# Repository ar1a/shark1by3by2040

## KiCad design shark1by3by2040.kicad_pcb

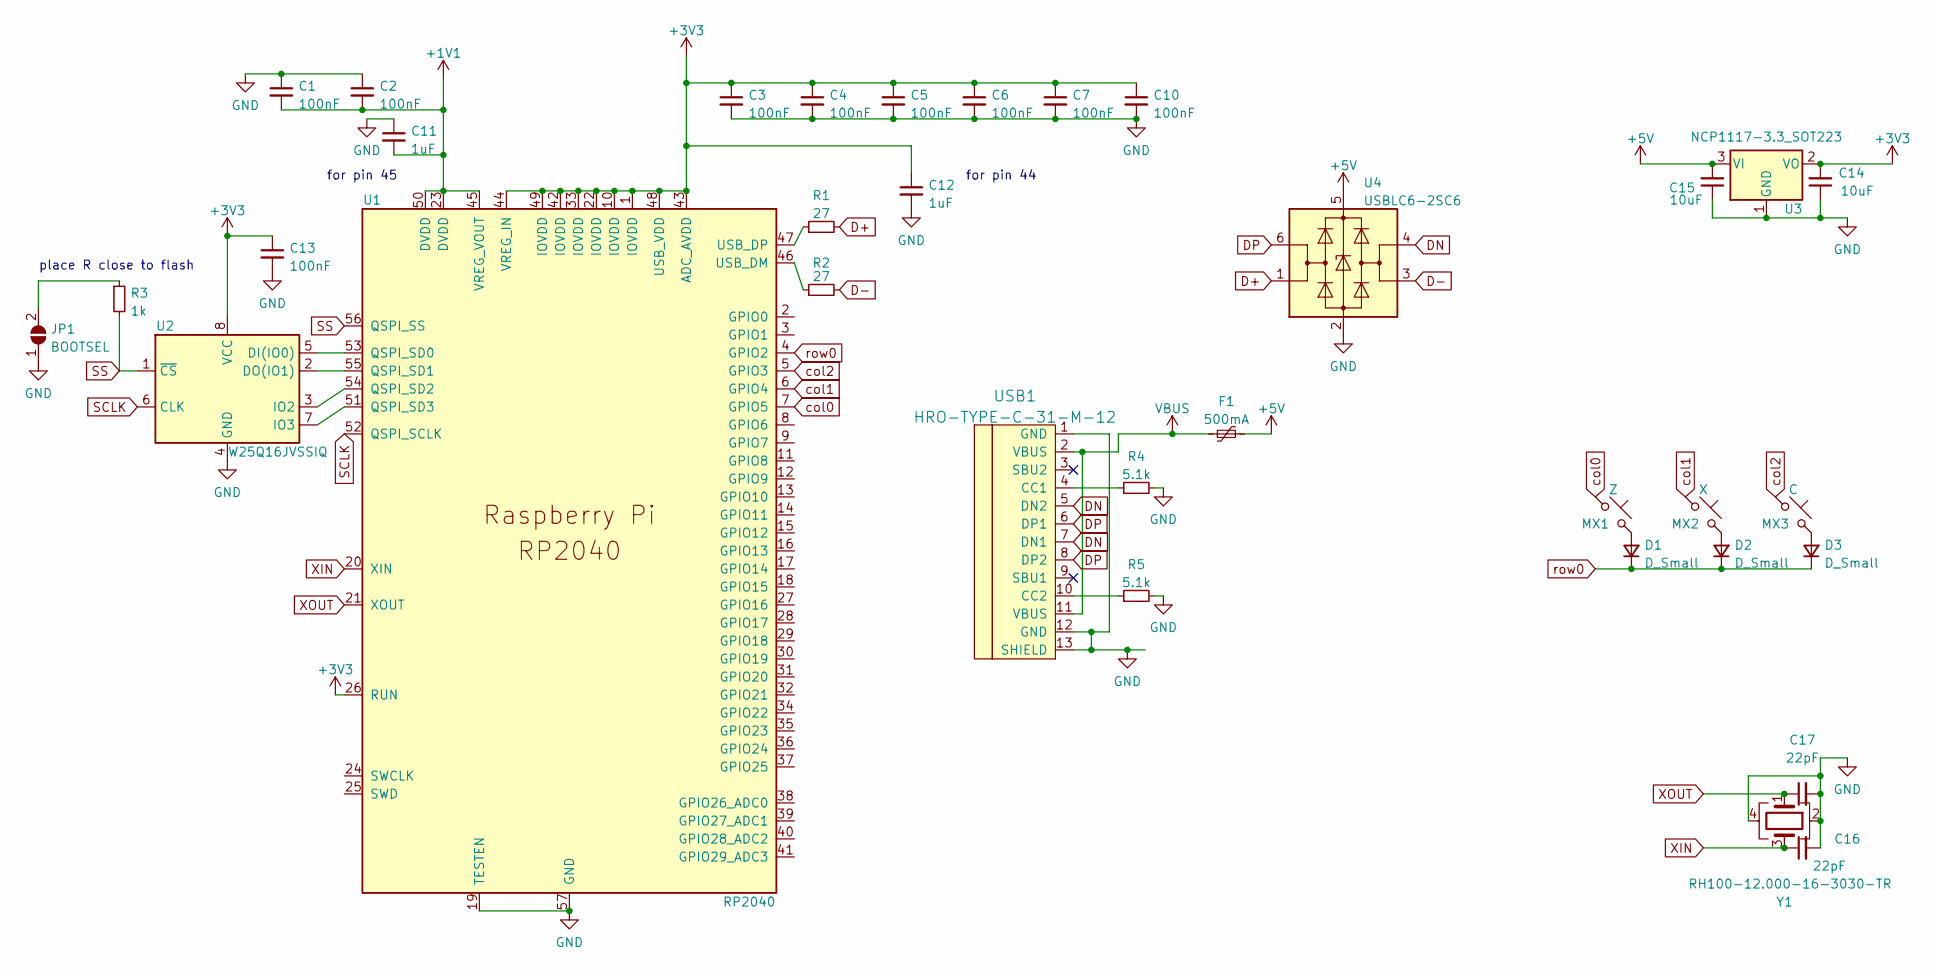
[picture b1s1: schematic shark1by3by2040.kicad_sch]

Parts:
C1, C2, C3, C4, C5, C6, C7, C10, C13: 100nF; C_0402_1005Metric
C11, C12: 1uF; C_0402_1005Metric
C14, C15: 10uF; C_0402_1005Metric
C16, C17: 22pF; C_0402_1005Metric
D1, D2, D3: D_Small; D_SOD-123-Pretty
F1: 500mA; Fuse_0805_2012Metric
JP1: BOOTSEL; Jumper-UserFriendly-Small
MX1: Z; SW_MX_HS_1u
MX2: X; SW_MX_HS_1u
MX3: C; SW_MX_HS_1u
R1, R2: 27; R_0402_1005Metric
R3: 1k; R_0402_1005Metric
R4, R5: 5.1k; R_0402_1005Metric
U1: RP2040; RP2040-QFN-56
U2: W25Q16JVSSIQ; SOIC-8_5.23x5.23mm_P1.27mm
U3: NCP1117-3.3_SOT223; SOT-223-3_TabPin2
U4: USBLC6-2SC6; SOT-23-6
USB1: HRO-TYPE-C-31-M-12; HRO-TYPE-C-31-M-12-Assembly
Y1: RH100-12.000-16-3030-TR; Crystal_SMD_3225-4Pin_3.2x2.5mm

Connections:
+1V1: C1.2, C2.2, C11.2, U1.23 (DVDD), U1.45 (VREG_VOUT), U1.50 (DVDD)
+3V3: C3.1, C4.1, C5.1, C6.1, C7.1, C10.1, C12.1, C13.1, C14.2, U1.1 (IOVDD), U1.10 (IOVDD), U1.22 (IOVDD), U1.26 (RUN), U1.33 (IOVDD), U1.42 (IOVDD), U1.43 (ADC_AVDD), U1.44 (VREG_IN), U1.48 (USB_VDD), U1.49 (IOVDD), U2.8 (VCC), U3.2 (VO)
+5V: C15.2, F1.2, U3.3 (VI), U4.5 (VBUS)
D+: R1.2, U4.1 (I/O1)
D-: R2.2, U4.3 (I/O2)
DN: U4.4 (I/O2), USB1.5 (DN2), USB1.7 (DN1)
DP: U4.6 (I/O1), USB1.6 (DP1), USB1.8 (DP2)
GND: C1.1, C2.1, C3.2, C4.2, C5.2, C6.2, C7.2, C10.2, C11.1, C12.2, C13.2, C14.1, C15.1, C16.2, C17.2, JP1.1 (A), R4.2, R5.2, U1.19 (TESTEN), U1.57 (GND), U2.4 (GND), U3.1 (GND), U4.2 (GND), USB1.1 (GND), USB1.12 (GND), USB1.13 (SHIELD), Y1.2, Y1.4
unnamed: D1.2 (A), MX1.2
unnamed: D2.2 (A), MX2.2
unnamed: D3.2 (A), MX3.2
unnamed: R1.1, U1.47 (USB_DP)
unnamed: R2.1, U1.46 (USB_DM)
unnamed: JP1.2 (B), R3.1
unnamed: R4.1, USB1.4 (CC1)
unnamed: R5.1, USB1.10 (CC2)
unnamed: U1.51 (QSPI_SD3), U2.7 (IO3)
unnamed: U1.53 (QSPI_SD0), U2.5 (DI(IO0))
unnamed: U1.54 (QSPI_SD2), U2.3 (IO2)
unnamed: U1.55 (QSPI_SD1), U2.2 (DO(IO1))
SCLK: U1.52 (QSPI_SCLK), U2.6 (CLK)
SS: R3.2, U1.56 (QSPI_SS), U2.1 (~CS)
VBUS: F1.1, USB1.2 (VBUS), USB1.11 (VBUS)
XIN: C16.1, U1.20 (XIN), Y1.3
XOUT: C17.1, U1.21 (XOUT), Y1.1
col0: MX1.1, U1.7 (GPIO5)
col1: MX2.1, U1.6 (GPIO4)
col2: MX3.1, U1.5 (GPIO3)
row0: D1.1 (K), D2.1 (K), D3.1 (K), U1.4 (GPIO2)

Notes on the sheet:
for pin 45
place R close to flash
for pin 44

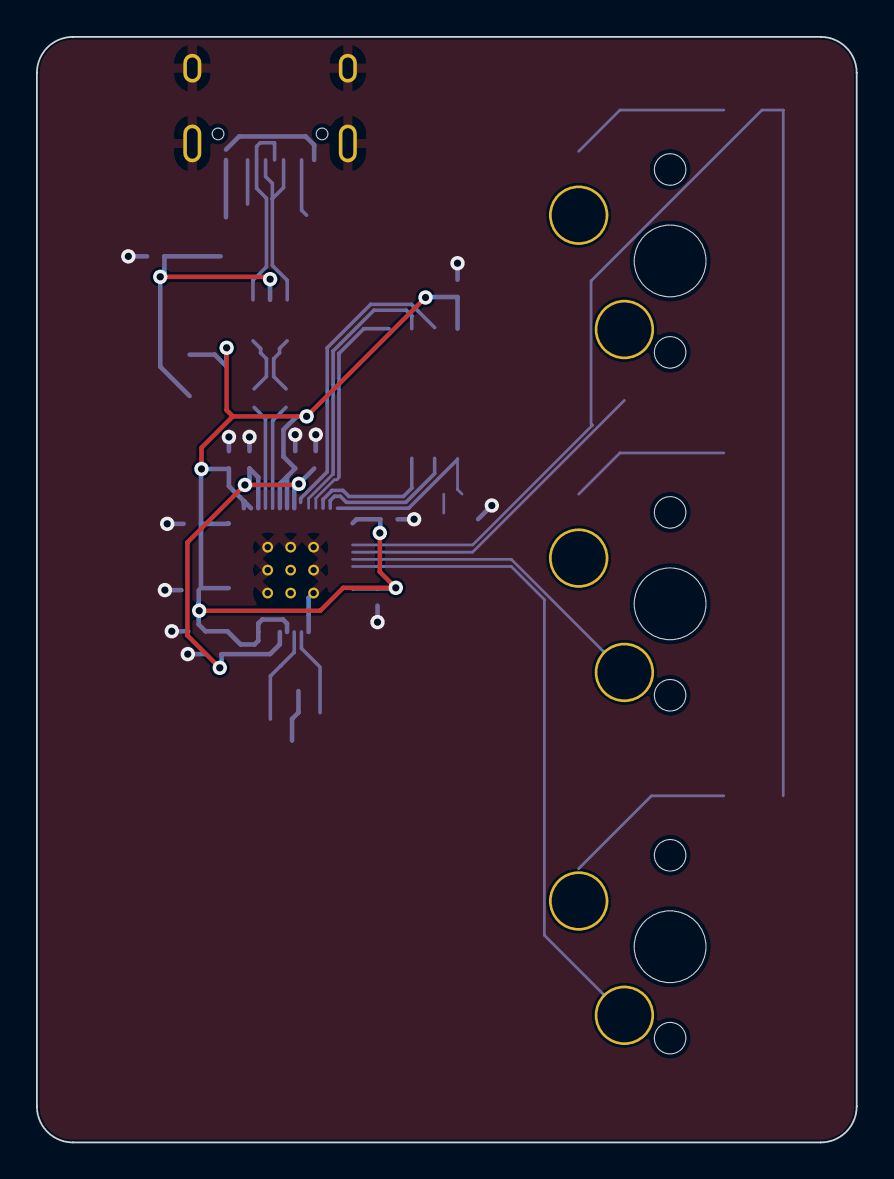
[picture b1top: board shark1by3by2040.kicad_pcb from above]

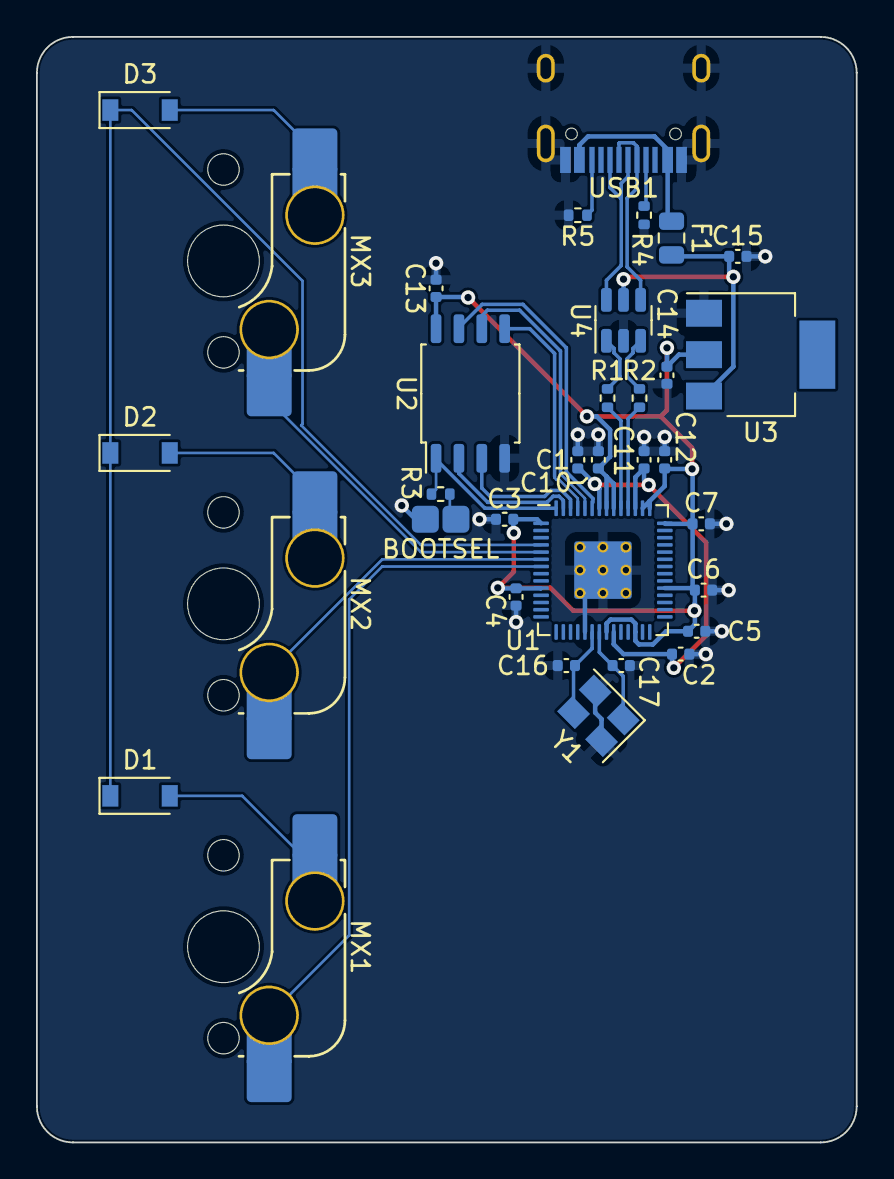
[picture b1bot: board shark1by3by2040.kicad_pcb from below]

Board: 2 copper layers, 45.5 x 61.4 mm, 34 parts (34 on the bottom side), 29 nets.

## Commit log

2022-05-24 init
2022-05-24 add uhhhhhhhhhh
2022-05-24 basic working rp2040
2022-05-26 make 1by3, do most of work on pcb
2022-05-27 1by3by2040 rev1
2022-05-27 1by3by2040 rev2
2022-05-27 add license
2022-05-27 add 3d model to rp2040
